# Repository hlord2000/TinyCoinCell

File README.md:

# TinyCoinCell

TinyCoinCell is a compact KiCad reference design for a coin-cell powered
Nordic beacon built around the nRF54L15, optional nPM2100 primary-cell PMIC,
and an ADXL367 accelerometer.

## Hardware

- nRF54L15 low-power Bluetooth LE 6 SoC, 1.5 MB NVM, 256 KB RAM, Arm Cortex-M33,
  and RISC-V coprocessor
- Optional nPM2100 primary-cell PMIC with fuel gauge and hibernate support
- ADXL367 ultralow-power accelerometer on I2C
- CR2032 battery holder
- User button and user LED
- SWD programming pads and UART breakout pads
- 32 MHz HF crystal and 32.768 kHz LF crystal

## Assembly Variants

| Variant | Populate | Do not populate | Notes |
| --- | --- | --- | --- |
| `nPM2100` | `U8`, `C44-C47`, `C49`, `L6`, `R3` | `R4`, `R7` | Button is connected to the nPM2100 ship-button input. The host can observe it through `nPM2100.GPIO0` on `P1.05`. |
| `No nPM2100` | `R4`, `R7` | `U8`, `C44-C47`, `C49`, `L6`, `R3` | Battery powers the board directly and the user button is connected to `P1.11`. |

Both variants omit the test pads from production placement files. The KiCad
variants also override `R5` and `R6` to `4.7kR`.

## Pinout

| Function | nRF54L15 pin |
| --- | --- |
| User LED | `P1.02` |
| I2C SDA | `P1.03` |
| I2C SCL | `P1.04` |
| nPM2100 GPIO0 | `P1.05` |
| User button, no-nPM2100 variant | `P1.11` |
| UART TX | `P2.00` |
| UART RX | `P2.02` |

This project uses symbols and footprints from
[nordic-lib-kicad](https://github.com/hlord2000/nordic-lib-kicad)

## Release Artifacts

The `v2` release is built from the contents of the local `build/` directory.
It includes the rendered board images, schematic PDF, STEP model, Gerbers, BOMs,
placement files, KiCad ERC/DRC reports, and the generated design-review bundle.

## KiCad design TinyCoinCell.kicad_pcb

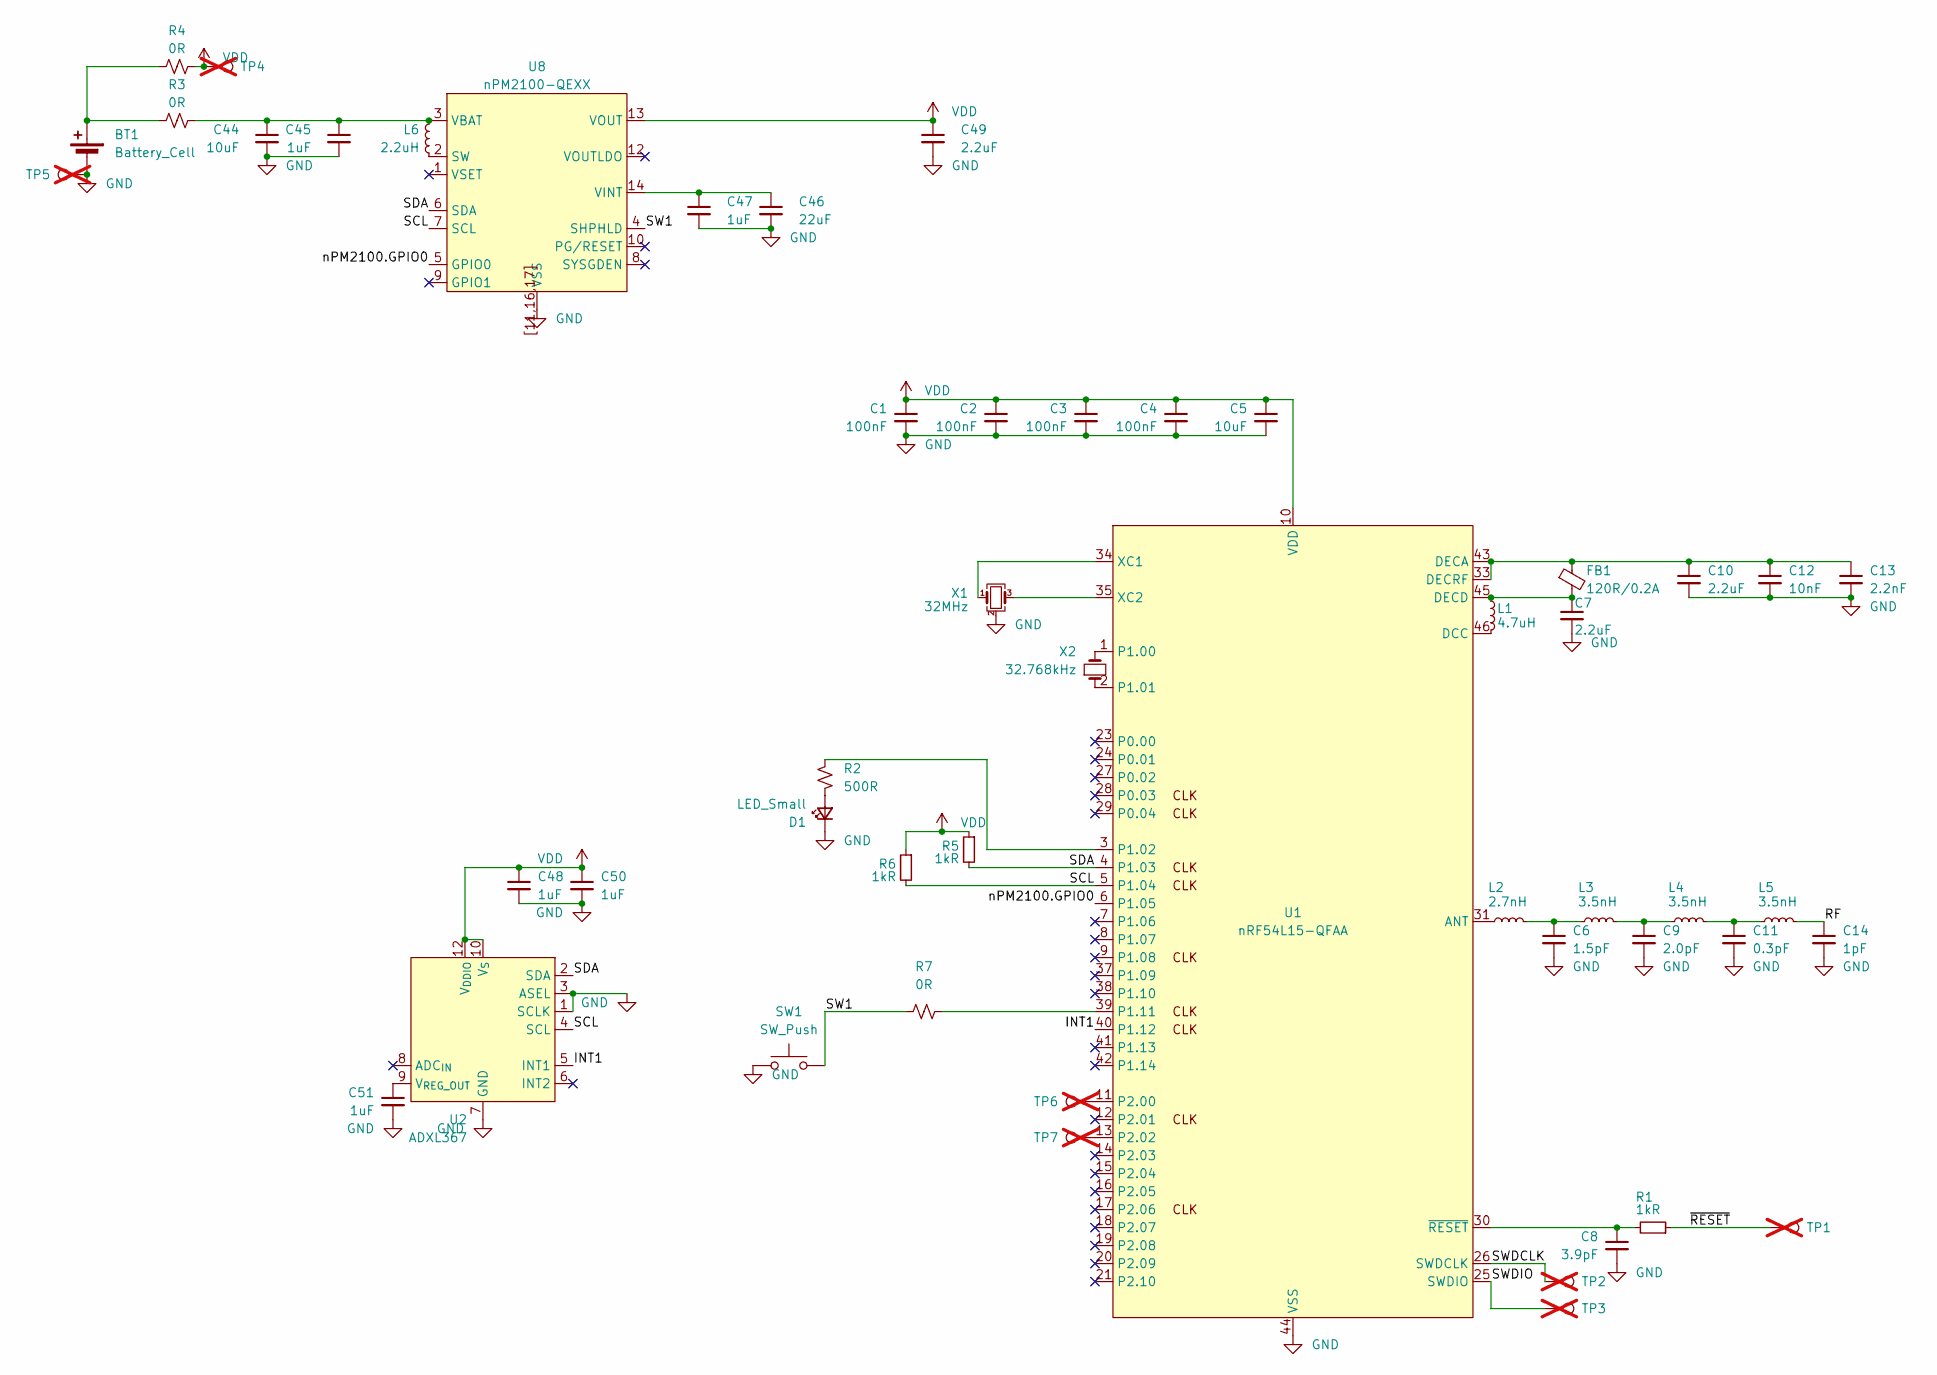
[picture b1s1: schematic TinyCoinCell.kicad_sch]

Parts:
BT1: Battery_Cell; BAT-TH_BAT-HLD-001-THM_1; LCSC C22417572
C1, C2, C3, C4: 100nF; C_0201_0603Metric_L; LCSC C2903664
C5: 10uF; C_0402_1005Metric_L; LCSC C15525
C6: 1.5pF; C_0201_0603Metric_L; LCSC C18164554
C7, C10: 2.2uF; C_0201_0603Metric_L; LCSC C5377657
C8: 3.9pF; C_0201_0603Metric_L; LCSC C18164580
C9: 2.0pF; C_0201_0603Metric_L; LCSC C18164556
C11: 0.3pF; C_0201_0603Metric_L; LCSC C723329
C12: 10nF; C_0201_0603Metric_L; LCSC C7393836
C13: 2.2nF; C_0201_0603Metric_L; LCSC C5142540
C14: 1pF; C_0201_0603Metric_L; LCSC C723329
C44: 10uF; C_0402_1005Metric; LCSC C15525
C45, C47, C48, C50, C51: 1uF; C_0201_0603Metric; LCSC C76930
C46: 22uF; C_0402_1005Metric; LCSC C385994
C49: 2.2uF; C_0201_0603Metric; LCSC C319184
D1: LED_Small; LED_0603_1608Metric; LCSC C52675989
FB1: 120R/0.2A; L_0201_0603Metric_L; LCSC C97850
L1: 4.7uH; L_0603_1608Metric_L; LCSC C295681
L2: 2.7nH; L_0201_0603Metric_L; LCSC C370148
L3, L4, L5: 3.5nH; L_0201_0603Metric_L; LCSC C52109755
L6: 2.2uH; L_0603_1608Metric; LCSC C394950
R1, R5, R6: 1kR; R_0201_0603Metric_L; LCSC C102683
R2: 500R; R_0402_1005Metric; LCSC C4125
R3, R4, R7: 0R; R_0402_1005Metric; LCSC C17168
SW1: SW_Push; SW_Push_1P1T_NO_Vertical_Wuerth_434133025816; LCSC C139797
TP1, TP2, TP3, TP4, TP5, TP6, TP7: TestPoint; TestPoint_Pad_D1.0mm; not fitted
U1: nRF54L15-QFAA; QFN-48-1EP_6x6mm_P0.4mm_EP4.6x4.6mm_ThermalVias; LCSC C42458750
U2: ADXL367; ADXL367_LGA-12_2.11x2.21mm_P0.5mm_LayoutBorder2x4y; LCSC C7424127
U8: nPM2100-QEXX; UQFN-16-1EP_4x4mm_P0.65mm_EP2.6x2.6mm_ThermalVias; LCSC C46968654
X1: 32MHz; Crystal_SMD_2016-4Pin_2.0x1.6mm; LCSC C2965582
X2: 32.768kHz; Crystal_SMD_2012-2Pin_2.0x1.2mm; LCSC C2838163

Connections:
/INT1: U1.40 (P1.12), U2.5 (INT1)
/RF: C14.1, L5.2
/SCL: R6.2, U1.5 (P1.04), U2.4 (SCL), U8.7 (SCL)
/SDA: R5.2, U1.4 (P1.03), U2.2 (SDA), U8.6 (SDA)
/SW1: R7.2, SW1.1, U8.4 (SHPHLD)
/SWDCLK: TP2.1 (1_1), U1.26 (SWDCLK)
/SWDIO: TP3.1 (1_1), U1.25 (SWDIO)
/nPM2100.GPIO0: U1.6 (P1.05), U8.5 (GPIO0)
/~RESET: R1.1, TP1.1 (1_1)
GND: BT1.2 (-), C1.2, C2.2, C3.2, C4.2, C5.2, C6.2, C7.2, C8.2, C9.2, C10.2, C11.2, C12.2, C13.2, C14.2, C44.2, C45.2, C46.2, C47.2, C48.2, C49.2, C50.2, C51.2, D1.1 (K), SW1.2, TP5.1 (1_1), U1.32 (VSS_PA), U1.44 (VSS), U1.49 (VSS), U2.1 (SCLK), U2.3 (ASEL), U2.7 (GND), U2.11 (GND), U8.11 (VSS), U8.16 (VSS), U8.17 (VSS), U8.[11,16,17] (VSS), X1.2 (G), X1.4 (G)
unnamed: BT1.1 (+), R3.1, R4.1
unnamed: C6.1, L2.2, L3.1
unnamed: C9.1, L3.2, L4.1
unnamed: C11.1, L4.2, L5.1
unnamed: C46.1, C47.1, U8.14 (VINT), U8.15 (VINT)
unnamed: D1.2 (A), R2.2
unnamed: L2.1, U1.31 (ANT)
unnamed: L1.2, U1.46 (DCC)
unnamed: C10.1, C12.1, C13.1, FB1.1, U1.33 (DECRF), U1.43 (DECA)
unnamed: C7.1, FB1.2, L1.1, U1.45 (DECD)
unnamed: U1.1 (P1.00), X2.2
unnamed: U1.2 (P1.01), X2.1
unnamed: R2.1, U1.3 (P1.02)
unnamed: R7.1, U1.39 (P1.11)
unnamed: TP6.1 (1_1), U1.11 (P2.00)
unnamed: TP7.1 (1_1), U1.13 (P2.02)
unnamed: U1.34 (XC1), X1.1
unnamed: U1.35 (XC2), X1.3
unnamed: C8.1, R1.2, U1.30 (~RESET)
unnamed: C51.1, U2.9 (V_{REG_OUT})
unnamed: L6.2, U8.2 (SW)
unnamed: C44.1, C45.1, L6.1, R3.2, U8.3 (VBAT)
VDD: C1.1, C2.1, C3.1, C4.1, C5.1, C48.1, C49.1, C50.1, R4.2, R5.1, R6.1, TP4.1 (1_1), U1.10 (VDD), U1.22 (VDD), U1.36 (VDD), U1.47 (VDD), U1.48 (VDD), U2.10 (V_{S}), U2.12 (V_{DDIO}), U8.13 (VOUT)

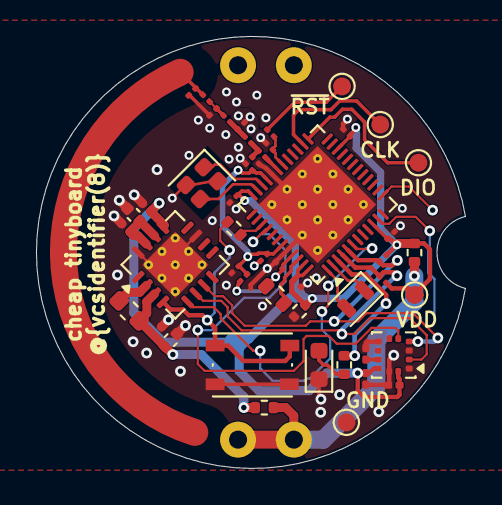
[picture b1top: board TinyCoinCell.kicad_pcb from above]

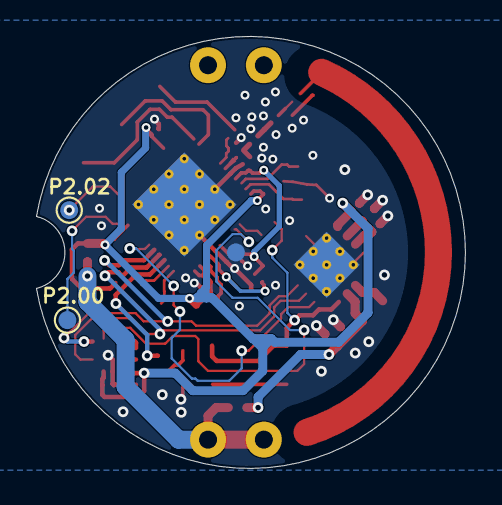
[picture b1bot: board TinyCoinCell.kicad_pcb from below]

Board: 4 copper layers, 23.8 x 24.0 mm, 51 parts (3 on the bottom side), 33 nets.

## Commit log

2026-06-03 Initial commit.
2026-06-03 Updated with BOM
2026-06-13 Updates for nPM2100
2026-06-16 Update for nPM2100, ADXL367
2026-06-16 Document TinyCoinCell v2 release
2026-06-16 Updated PCB
2026-06-16 Point README at build release images
2026-06-16 Use local README board image
2026-06-23 Updates for manufacturing
